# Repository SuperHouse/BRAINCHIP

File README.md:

Building Brain Home Automation Controller (CHIP version)
=========================================================
Copyright 2017 SuperHouse Automation Pty Ltd  www.superhouse.tv  

Home automation controller based on a C.H.I.P. The CHIP
attaches to this board, which is Arduino-compatible (ATmega328P) and
includes 433MHz transmitter and receiver modules connected to the
Arduino. The Arduino can communicate with the CHIP via serial, and
can send / receive RF messages using the 433MHz modules.

Features:

 * ATmega328P MCU
 * 433MHz transmitter
 * 433MHz receiver
 * Status LEDs

INSTALLATION
------------
The design is saved as an EAGLE project. EAGLE PCB design software is
available from www.cadsoftusa.com free for non-commercial use. To use
this project download it and place the directory containing these files
into the "eagle" directory on your computer. Then open EAGLE and
navigate to the project.

CREDITS
-------
Designed by Jonathan Oxer jon@oxer.com.au

DISTRIBUTION
------------
The specific terms of distribution of this project are governed by the
license referenced below.

LICENSE
-------
Licensed under the TAPR Open Hardware License (www.tapr.org/OHL).
The "license" folder within this repository also contains a copy of
this license in plain text format.

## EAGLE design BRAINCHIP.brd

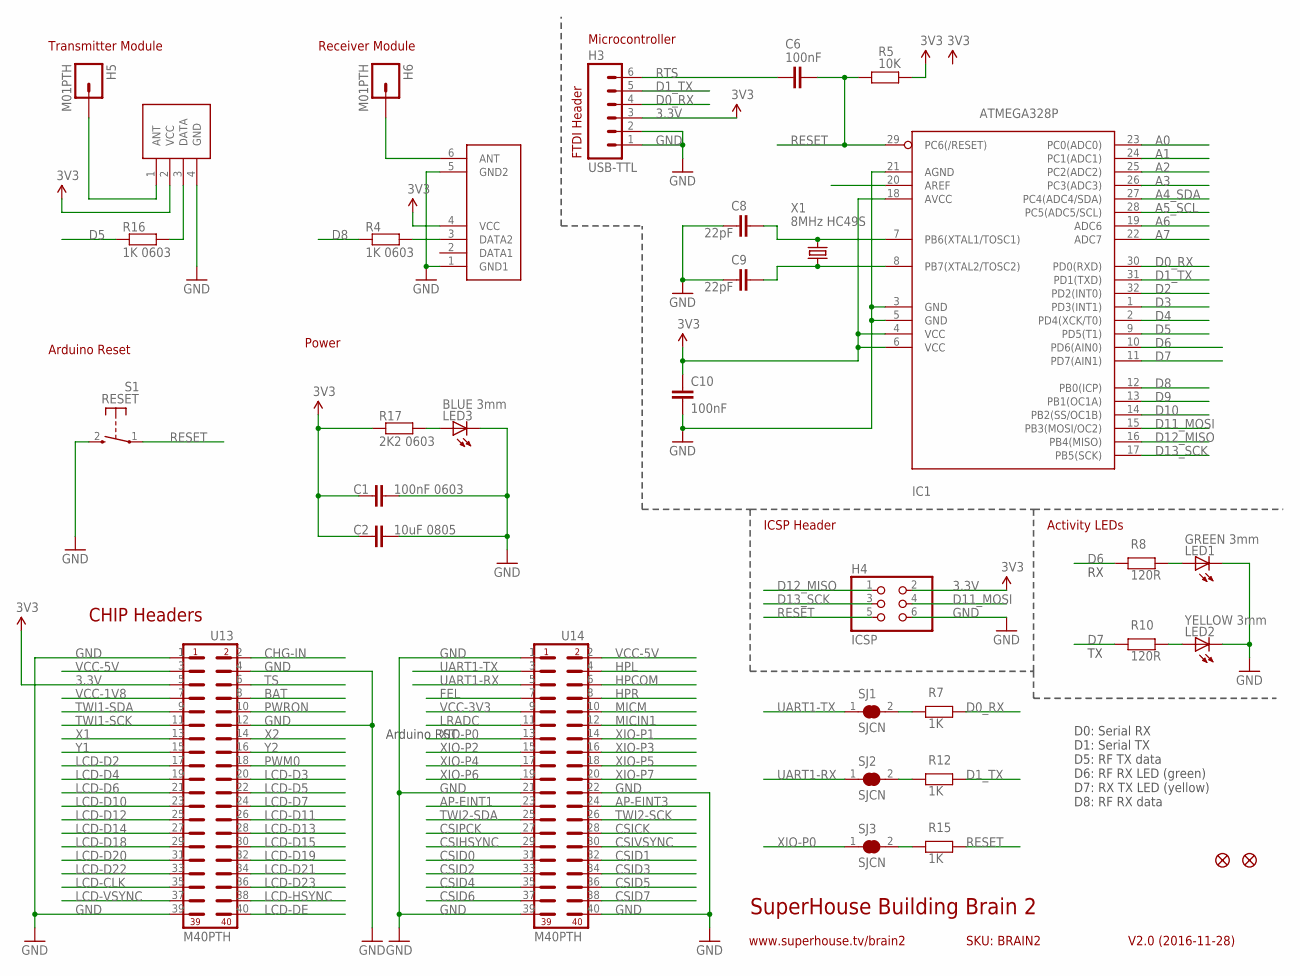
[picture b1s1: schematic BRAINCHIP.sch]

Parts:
C1: 100nF 0603; 0603
C2: 10uF 0805; C0805
C6, C10: 100nF; 0603
C8, C9: 22pF; 0603
H3: USB-TTL; 1X06
H4: ICSP; 2X03
H5, H6: M01PTH; 1X01
IC1: ATMEGA328P; TQFP32-08
IC3: RXB1; RX-B1-SHORT-FLAT
IC4: TX-C1FLAT; TX-C1-FLAT
LED1: GREEN 3mm; LED3MM
LED2: YELLOW 3mm; LED3MM
LED3: BLUE 3mm; LED3MM
R4, R16: 1K 0603; 0603
R5: 10K; 0603
R7, R12, R15: 1K; 0603
R8, R10: 120R; 0603
R17: 2K2 0603; 0603
S1: RESET; TACTILE_SWITCH_SMD_2PIN_TINY
SJ1, SJ2, SJ3: SJCN; SJC
U13, U14: M40PTH; 2X20
U$5, U$6: FIDUCIAL1X2.5; FIDUCIAL-1X2.5
X1: 8MHz HC49S; HC49U-V

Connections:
3.3V: C1.1, C2.2, C10.1, H3.3, H4.2, IC1.4 (VCC), IC1.6 (VCC), IC1.18 (AVCC), IC3.4 (VCC), IC4.2 (VCC), R5.2, R17.1, U13.5
A0: IC1.23 (PC0(ADC0))
A1: IC1.24 (PC1(ADC1))
A2: IC1.25 (PC2(ADC2))
A3: IC1.26 (PC3(ADC3))
A4_SDA: IC1.27 (PC4(ADC4/SDA))
A5_SCL: IC1.28 (PC5(ADC5/SCL))
A6: IC1.19 (ADC6)
A7: IC1.22 (ADC7)
AP-EINT1: U14.23
AP-EINT3: U14.24
AREF: IC1.20 (AREF)
BAT: U13.8
CHG-IN: U13.2
CSICK: U14.28
CSID0: U14.31
CSID1: U14.32
CSID2: U14.33
CSID3: U14.34
CSID4: U14.35
CSID5: U14.36
CSID6: U14.37
CSID7: U14.38
CSIHSYNC: U14.29
CSIPCK: U14.27
CSIVSYNC: U14.30
D0_RX: H3.4, IC1.30 (PD0(RXD)), R7.1
D1_TX: H3.5, IC1.31 (PD1(TXD)), R12.1
D2: IC1.32 (PD2(INT0))
D3: IC1.1 (PD3(INT1))
D4: IC1.2 (PD4(XCK/T0))
D5: IC1.9 (PD5(T1)), R16.1
D6: IC1.10 (PD6(AIN0)), R8.2
D7: IC1.11 (PD7(AIN1)), R10.2
D8: IC1.12 (PB0(ICP)), R4.1
D9: IC1.13 (PB1(OC1A))
D10: IC1.14 (PB2(SS/OC1B))
D11_MOSI: H4.4, IC1.15 (PB3(MOSI/OC2))
D12_MISO: H4.1, IC1.16 (PB4(MISO))
D13_SCK: H4.3, IC1.17 (PB5(SCK))
FEL: U14.7
GND: C1.2, C2.1, C8.1, C9.1, C10.2, H3.1, H3.2, H4.6, IC1.3 (GND), IC1.5 (GND), IC1.21 (AGND), IC3.1 (GND1), IC3.5 (GND2), IC4.4 (GND), LED1.K (C), LED2.K (C), LED3.K (C), S1.2 (S), U13.1, U13.4, U13.12, U13.39, U14.1, U14.21, U14.22, U14.39, U14.40
HPCOM: U14.6
HPL: U14.4
HPR: U14.8
LCD-CLK: U13.35
LCD-D2: U13.17
LCD-D3: U13.20
LCD-D4: U13.19
LCD-D5: U13.22
LCD-D6: U13.21
LCD-D7: U13.24
LCD-D10: U13.23
LCD-D11: U13.26
LCD-D12: U13.25
LCD-D13: U13.28
LCD-D14: U13.27
LCD-D15: U13.30
LCD-D18: U13.29
LCD-D19: U13.32
LCD-D20: U13.31
LCD-D21: U13.34
LCD-D22: U13.33
LCD-D23: U13.36
LCD-DE: U13.40
LCD-HSYNC: U13.38
LCD-VSYNC: U13.37
LRADC: U14.11
MICIN1: U14.12
MICM: U14.10
unnamed: IC3.3 (DATA2), R4.2
unnamed: LED3.A, R17.2
unnamed: H6.1, IC3.6 (ANT)
unnamed: H5.1, IC4.1 (ANT)
unnamed: IC4.3 (DATA), R16.2
unnamed: C8.2, IC1.7 (PB6(XTAL1/TOSC1)), X1.2
unnamed: C9.2, IC1.8 (PB7(XTAL2/TOSC2)), X1.1
unnamed: LED1.A, R8.1
unnamed: LED2.A, R10.1
unnamed: R7.2, SJ1.2
unnamed: R12.2, SJ2.2
unnamed: R15.2, SJ3.2
PWM0: U13.18
PWRON: U13.10
RESET: C6.2, H4.5, IC1.29 (PC6(/RESET)), R5.1, R15.1, S1.1
RTS: C6.1, H3.6
TS: U13.6
TWI1-SCK: U13.11
TWI1-SDA: U13.9
TWI2-SCK: U14.26
TWI2-SDA: U14.25
UART1-RX: SJ2.1, U14.5
UART1-TX: SJ1.1, U14.3
VCC-1V8: U13.7
VCC-3V3: U14.9
VCC-5V: U13.3, U14.2
X1: U13.13
X2: U13.14
XIO-P0: SJ3.1, U14.13
XIO-P1: U14.14
XIO-P2: U14.15
XIO-P3: U14.16
XIO-P4: U14.17
XIO-P5: U14.18
XIO-P6: U14.19
XIO-P7: U14.20
Y1: U13.15
Y2: U13.16

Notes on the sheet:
CHIP Headers
Power
Receiver Module
D0: Serial RX D1: Serial TX D5: RF TX data D6: RF RX LED (green) D7: RX TX LED (yellow) D8: RF RX data
ICSP Header
Microcontroller
FTDI Header
Transmitter Module
Arduino Reset
Activity LEDs
Arduino RST
SuperHouse Building Brain 2
V2.0 (2016-11-28)
www.superhouse.tv/brain2
SKU: BRAIN2

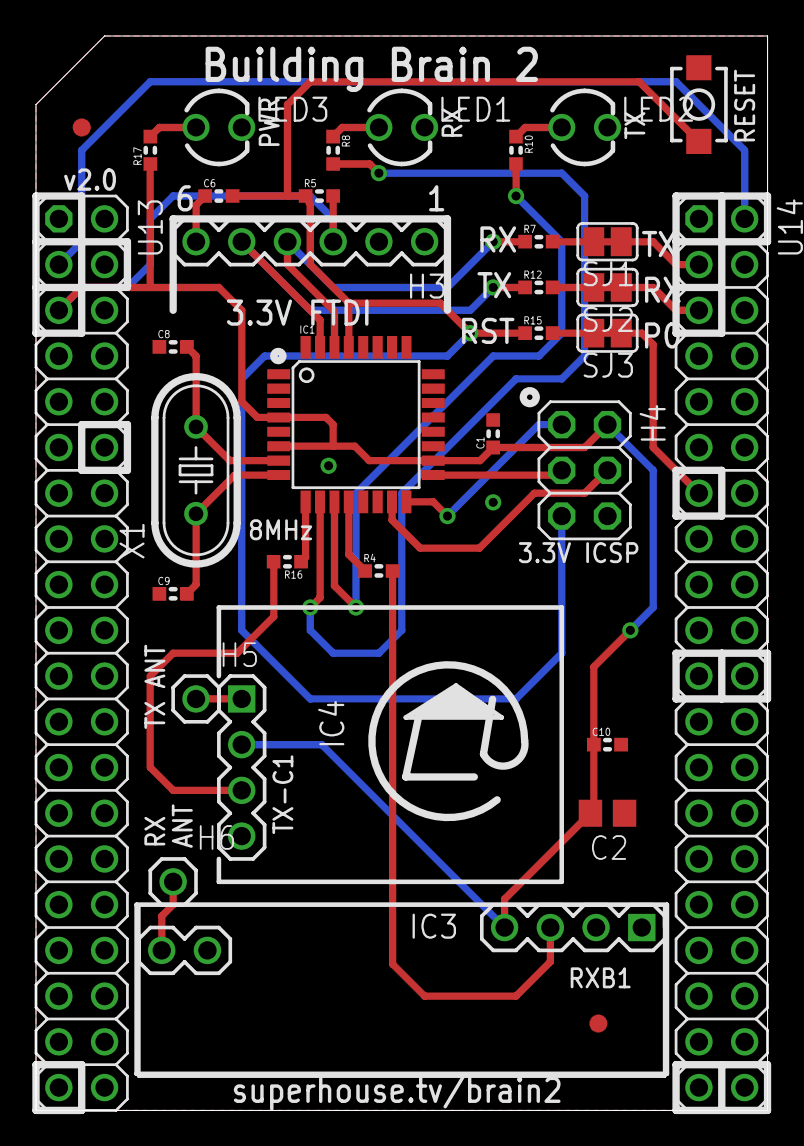
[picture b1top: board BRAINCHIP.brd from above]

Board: 2 copper layers, 40.6 x 59.7 mm, 34 parts (0 on the bottom side), 29 nets.

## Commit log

2018-03-23 Initial project import

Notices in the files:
BRAINCHIP.brd:
(c) 2016 SuperHouse Automation
